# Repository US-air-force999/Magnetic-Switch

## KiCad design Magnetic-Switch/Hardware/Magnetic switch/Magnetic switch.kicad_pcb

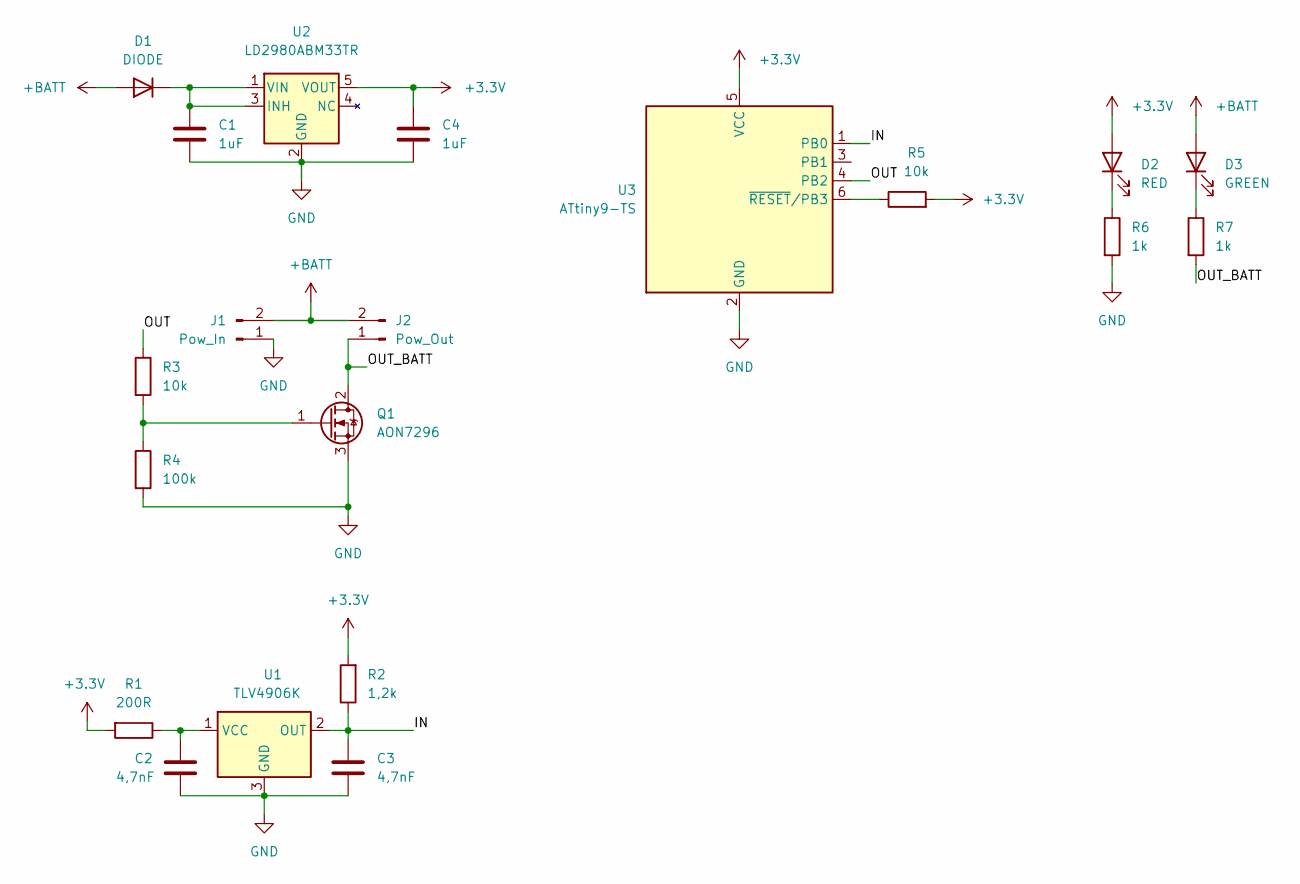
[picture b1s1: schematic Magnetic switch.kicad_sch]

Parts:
C1, C4: 1uF; C_0805_2012Metric
C2, C3: 4,7nF; C_0402_1005Metric
D1: DIODE; D_0805_2012Metric
D2: RED; LED_0402_1005Metric
D3: GREEN; LED_0402_1005Metric
J1: Pow_In; 1 pad tht
J2: Pow_Out; 1 pad tht
Q1: AON7296; DFN-8-1EP_3x3mm_P0.65mm_EP1.7x2.05mm
R1: 200R; R_0402_1005Metric
R2: 1,2k; R_0402_1005Metric
R3, R5: 10k; R_0402_1005Metric
R4: 100k; R_0402_1005Metric
R6, R7: 1k; R_0402_1005Metric
U1: TLV4906K; SC-59
U2: LD2980ABM33TR; SOT-23-5
U3: ATtiny9-TS; SOT-23-6

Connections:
+3V3: C4.1, D2.2 (A), R1.2, R2.2, R5.2, U2.5 (VOUT), U3.5 (VCC)
+BATT: D1.1 (A), D3.2 (A), J1.2, J2.2
/IN: C3.1, R2.1, U1.2 (OUT), U3.1 (PB0)
/OUT: R3.1, U3.4 (PB2)
/OUT_BATT: J2.1, Q1.2 (D), R7.2
GND: C1.2, C2.2, C3.2, C4.2, J1.1, Q1.3 (S), R4.2, R6.2, U1.3 (GND), U2.2 (GND), U3.2 (GND)
unnamed: C1.1, D1.2 (K), U2.1 (VIN), U2.3 (INH)
unnamed: C2.1, R1.1, U1.1 (VCC)
unnamed: D2.1 (K), R6.1
unnamed: D3.1 (K), R7.1
unnamed: Q1.1 (G), R3.2, R4.1
unnamed: R5.1, U3.6 (~RESET/PB3)

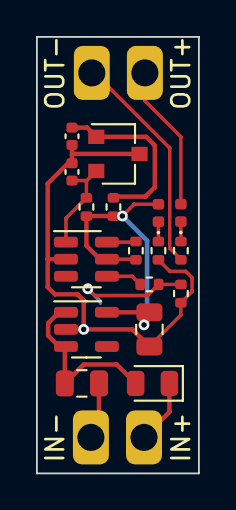
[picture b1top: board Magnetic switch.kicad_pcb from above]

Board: 2 copper layers, 9.0 x 24.2 mm, 20 parts (1 on the bottom side), 12 nets.
